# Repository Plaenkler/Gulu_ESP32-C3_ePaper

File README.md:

# Gulu ESP32-C3 ePaper Devboard

> No AI was involved in this project. Whether that is a mark of quality or the opposite is up to you.

<table>
  <tr>
    <td></td>
    <td></td>
  </tr>
</table>

## About Gulu ESP32-C3 ePaper

Introducing the **Gulu_ESP32-C3_ePaper** Devboard: a cutting-edge development board powered by the ESP32-C3.
This board features a modular power system, equipped with the [Egg_LDO_1000](https://github.com/Plaenkler/Egg_LDO_1000) by default for efficient performance.
Designed to support a wide range of ePaper displays from **WaveShare** and **Good Display** that require the 0.47 Ohm resistor.

## 📖 Specifications

 * MCU: ESP32-C3-WROOM-02-H4
 * Power supply: [Egg_LDO_1000](https://github.com/Plaenkler/Egg_LDO_1000)
 * Connectivity: SPI, UART/USB, 24-pin FPC ePaper connection

## ⚡ Circuit Diagram

## Power consumption

The power consumption in deep sleep mode of the ESP32-C3 was measured using the [Power Profiler Kit II](https://www.nordicsemi.com/Products/Development-hardware/Power-Profiler-Kit-2) from Nordic Semiconductor.
The example firmware in this project was used as a benchmark.
A daughter board such as the [Egg_LDO_1000](https://github.com/Plaenkler/Egg_LDO_1000) was not used, and VOUT and GND of the kit were connected directly to the corresponding pads.
During the measurement, a 7.5 inch black and white display ([WFT0583CZ61](https://www.good-display.com/product/396.html)) from [Good Display](https://www.good-display.com) was connected to the FPC port.
The duration of the measurement in this case was one minute after the first cycle of the firmware, which resulted in an average current of **~35μA**.
When the display is not connected, the current is approximately **~10μA** in deep sleep mode.

## Arduino compatibility

During the design phase of the Gulu, a custom set of IO pins was used for the 4-wire SPI connection.
In order for firmware based on the Arduino framework to work on the Gulu, adjustments must be made to the pin definitions.

```cpp
// Default esp32c3>pins_arduino.h
static const uint8_t SS    = 7;
static const uint8_t MOSI  = 6;
static const uint8_t MISO  = 5;
static const uint8_t SCK   = 4;

// Modified esp32c3>pins_arduino.h
static const uint8_t SS    = 7; // EPD_DC
static const uint8_t MOSI  = 4; // EPD_DIN
static const uint8_t MISO  = 6; // EPD_CS
static const uint8_t SCK   = 5; // EPD_SCK
```

## Firmware example

### Display Definition and Image

This section contains a header file with a definition for the display and a sample image.
The display is initialized with the required pins specified for the GxEPD2 library.
Additionally, a sample image is defined as an array of byte data stored in PROGMEM (program memory) of the microcontroller.

```cpp
#ifndef _750_T7_H_
#define _750_T7_H_

#include <GxEPD2_BW.h>

GxEPD2_BW<GxEPD2_750_T7, GxEPD2_750_T7::HEIGHT> display(
  GxEPD2_750_T7(6, 7, 10, 3)
);

const unsigned char image[] PROGMEM = {
    0x55, 0x55, 0x55, 0x6d, 0xb6, 0xdb, 0x6d, 0xb5, 0x6a, 0xbf, 0xf5, 0x22, ...
```

### Main Program

The first section initializes the necessary components for the firmware.
Firstly, the onboard LED (connected to pin 0) is configured as an output.
Then, the display initialization is called.

```cpp
#include "750_T7.h"

void setup() {
  pinMode(0, OUTPUT);
  display.init();
}
```

In the main part of the program, the sample picture is displayed on the screen, after which the screen is switched to hibernation mode.
Subsequently, the onboard LED is turned on for one second and then turned off.
After that, a timer wakeup for the deep sleep mode is enabled, and the microcontroller is put into deep sleep.

```cpp
void loop() {
  display.drawImage(image, 0, 0, 800, 480);
  display.hibernate();
  digitalWrite(0, 1);
  delay(1e3);
  digitalWrite(0, 0);
  esp_sleep_enable_timer_wakeup(1e7);
  esp_deep_sleep_start();
}
```

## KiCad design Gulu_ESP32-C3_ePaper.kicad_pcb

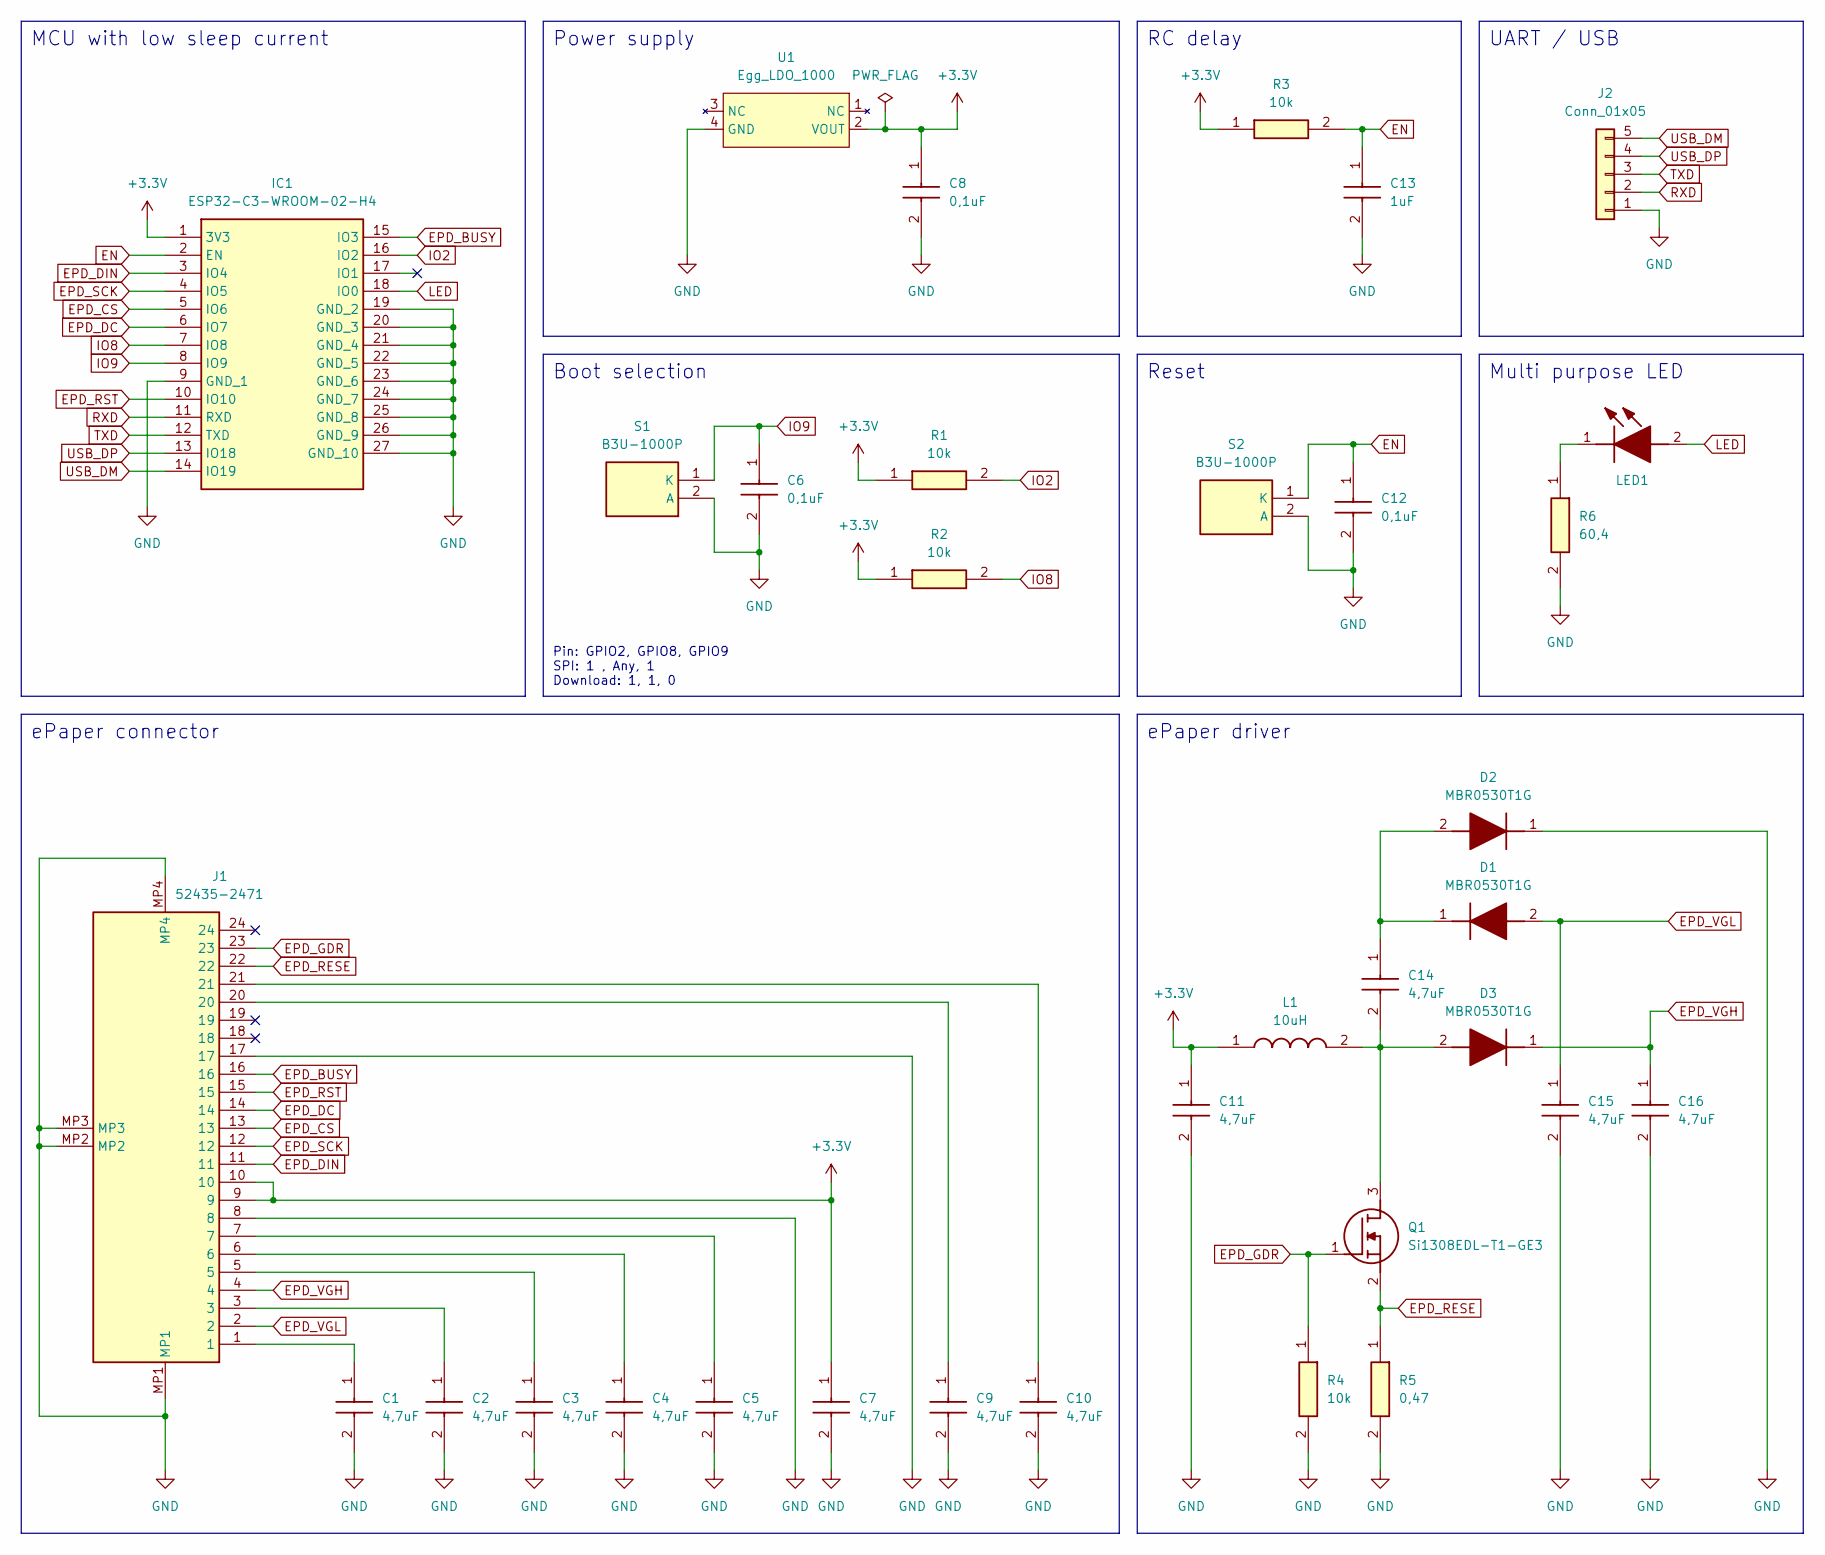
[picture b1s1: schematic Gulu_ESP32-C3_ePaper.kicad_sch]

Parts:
C1, C2, C3, C4, C5, C7, C9, C10, C11, C14, C15, C16: 4,7uF; CAPC1608X90N; Mouser Part Number 81-GRM188R6YA475KE5D
C6, C8, C12: 0,1uF; CAPC1608X90N; Mouser Part Number 581-KAM15AR71H104KM
C13: 1uF; CAPC1608X90N; Mouser Part Number 810-CGA3E1X7R1V105KC
D1, D2, D3: MBR0530T1G; SOD3716X135N; Mouser Part Number 863-MBR0530T1G
IC1: ESP32-C3-WROOM-02-H4; ESP32C3WROOM02H4; Mouser Part Number 356-ESP32C3WROOM02H4
J1: 52435-2471; 524352471; Mouser Part Number 538-52435-2471
J2: Conn_01x05; PinHeader_1x05_P2.54mm_Vertical
L1: 10uH; SRN3015; Mouser Part Number 652-SRN3015-100M
LED1: 598-2000-107F; 5982000107F; Manufacturer_Part_Number 598-2000-107F
Q1: Si1308EDL-T1-GE3; SOT65P210X110-3N; Mouser Part Number 78-SI1308EDL-T1-GE3
R1, R2, R3, R4: 10k; RESC1608X55N; Mouser Part Number 755-ESR03EZPF1002
R5: 0,47; RESC1608X60N; Mouser Part Number 71-RCWE0603R470FKEA
R6: 60,4; RESC2012X60N; Manufacturer_Part_Number AC0805FR-7W60R4L
S1, S2: B3U-1000P; Mouser Part Number 653-B3U-1000P
U1: Egg_LDO_1000

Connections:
+3.3V: C7.1, C8.1, C11.1, IC1.1 (3V3), J1.9, J1.10, L1.1, R1.1, R2.1, R3.1, U1.2 (VOUT)
EN: C12.1, C13.1, IC1.2 (EN), R3.2, S2.1 (K)
EPD_BUSY: IC1.15 (IO3), J1.16
EPD_CS: IC1.5 (IO6), J1.13
EPD_DC: IC1.6 (IO7), J1.14
EPD_DIN: IC1.3 (IO4), J1.11
EPD_GDR: J1.23, Q1.1 (G), R4.1
EPD_RESE: J1.22, Q1.2 (S), R5.1
EPD_RST: IC1.10 (IO10), J1.15
EPD_SCK: IC1.4 (IO5), J1.12
EPD_VGH: C16.1, D3.1 (K), J1.4
EPD_VGL: C15.1, D1.2 (A), J1.2
GND: C1.2, C2.2, C3.2, C4.2, C5.2, C6.2, C7.2, C8.2, C9.2, C10.2, C11.2, C12.2, C13.2, C15.2, C16.2, D2.1 (K), IC1.9 (GND_1), IC1.19 (GND_2), IC1.20 (GND_3), IC1.21 (GND_4), IC1.22 (GND_5), IC1.23 (GND_6), IC1.24 (GND_7), IC1.25 (GND_8), IC1.26 (GND_9), IC1.27 (GND_10), J1.8, J1.17, J1.MP1, J1.MP2, J1.MP3, J1.MP4, J2.1, R4.2, R5.2, R6.2, S1.2 (A), S2.2 (A), U1.4 (GND)
IO2: IC1.16 (IO2), R1.2
IO8: IC1.7 (IO8), R2.2
IO9: C6.1, IC1.8 (IO9), S1.1 (K)
LED: IC1.18 (IO0), LED1.2 (A)
unnamed: C1.1, J1.1
unnamed: C2.1, J1.3
unnamed: C3.1, J1.5
unnamed: C4.1, J1.6
unnamed: C5.1, J1.7
unnamed: C9.1, J1.20
unnamed: C10.1, J1.21
unnamed: C14.1, D1.1 (K), D2.2 (A)
unnamed: C14.2, D3.2 (A), L1.2, Q1.3 (D)
unnamed: LED1.1 (K), R6.1
RXD: IC1.11 (RXD), J2.2
TXD: IC1.12 (TXD), J2.3
USB_DM: IC1.14 (IO19), J2.5
USB_DP: IC1.13 (IO18), J2.4

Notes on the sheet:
ePaper connector
Multi purpose LED
MCU with low sleep current
RC delay
Reset
UART / USB
Boot selection
Pin: GPIO2, GPIO8, GPIO9 SPI: 1 , Any, 1 Download: 1, 1, 0
ePaper driver
Power supply

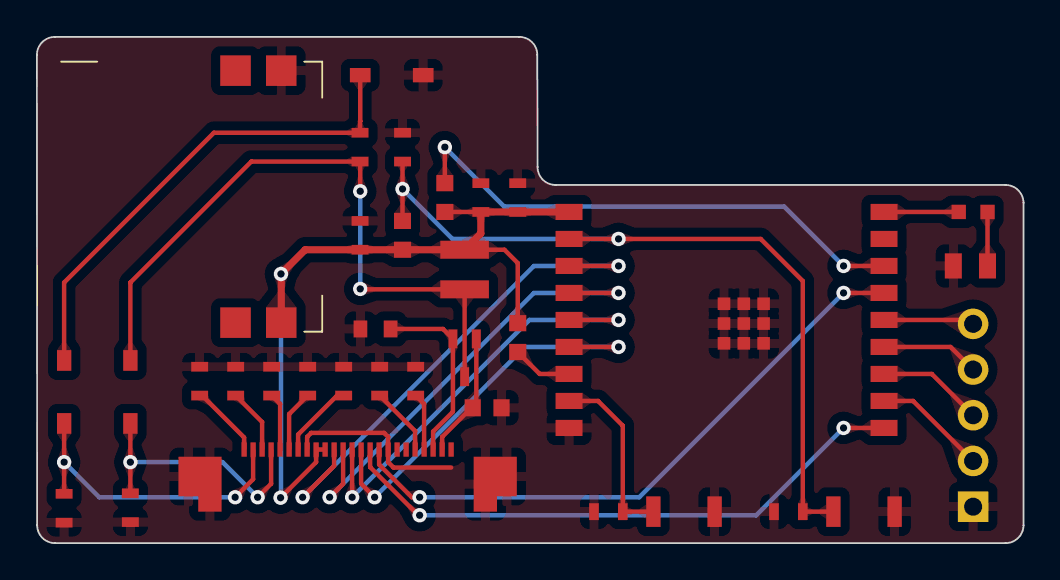
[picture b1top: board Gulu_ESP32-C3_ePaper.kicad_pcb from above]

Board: 2 copper layers, 54.8 x 28.1 mm, 34 parts (0 on the bottom side), 31 nets.

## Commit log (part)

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2024-01-28 [ADD] Current state
2024-01-28 [ADD] .gitignore
2024-01-28 [ADD] Funding information
2024-02-02 [UPD] 0805 components
2024-02-06 [UPD] Small 68uH coil
2024-02-08 [UPD] Reorganized IO pins
2024-02-19 [UPD] Revised circuit diagram
    - USB header added
    - Power supply replaced by Egg_LDO_1000
    - DIN and SCK pin assignment corrected
2024-02-22 [UPD] Completely new design
2024-02-22 [UPD] Added LED and relocated pins
2024-02-22 [ADD] 3D models
2024-02-22 [ADD] Interactive BOM
2024-02-23 [REM] Superfluous button
2024-02-23 [UPD] BOM -> 1.1.0
2024-03-05 [UPD] Replaced components
    0805 -> 0603
2024-03-05 [ADD] New 3D models
2024-03-05 [UPD] Version & interactive BOM
2024-03-05 [ADD] Alternative tag mpn
    Export alternative tag in BOM
2024-03-06 [FIX] References & teardrops
2024-03-07 [ADD] README.md
2024-04-05 [UPD] README.md
    Describe power consumption in deep sleep mode
2024-04-12 [ADD] Firmware example
2024-04-12 [FIX] Quail (Gulu) image
2024-04-18 [FIX] Use USB as serial output
2024-04-23 [UPD] monitor_filters
2024-04-23 [FIX] monitor_filters
    Do not log2file
2024-04-25 [FIX] Superfluous components
2024-04-26 [UPD] README.md
2024-04-26 [UPD] Moved display definition
